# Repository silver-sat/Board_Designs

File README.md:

# Board_Designs
KiCAD files for PC Board Designs
<br><br><strong>Due to technical issues, each board has been moved to their own repositories. Here are the links:</strong>
|Repository Links|                                              |
|--------------|------------------------------------------------|
| Avionics     | https://github.com/silver-sat/Avionics_Board   |
| Payload      | https://github.com/silver-sat/Payload_Board    |
| Radio        | https://github.com/silver-sat/Radio_Board      |

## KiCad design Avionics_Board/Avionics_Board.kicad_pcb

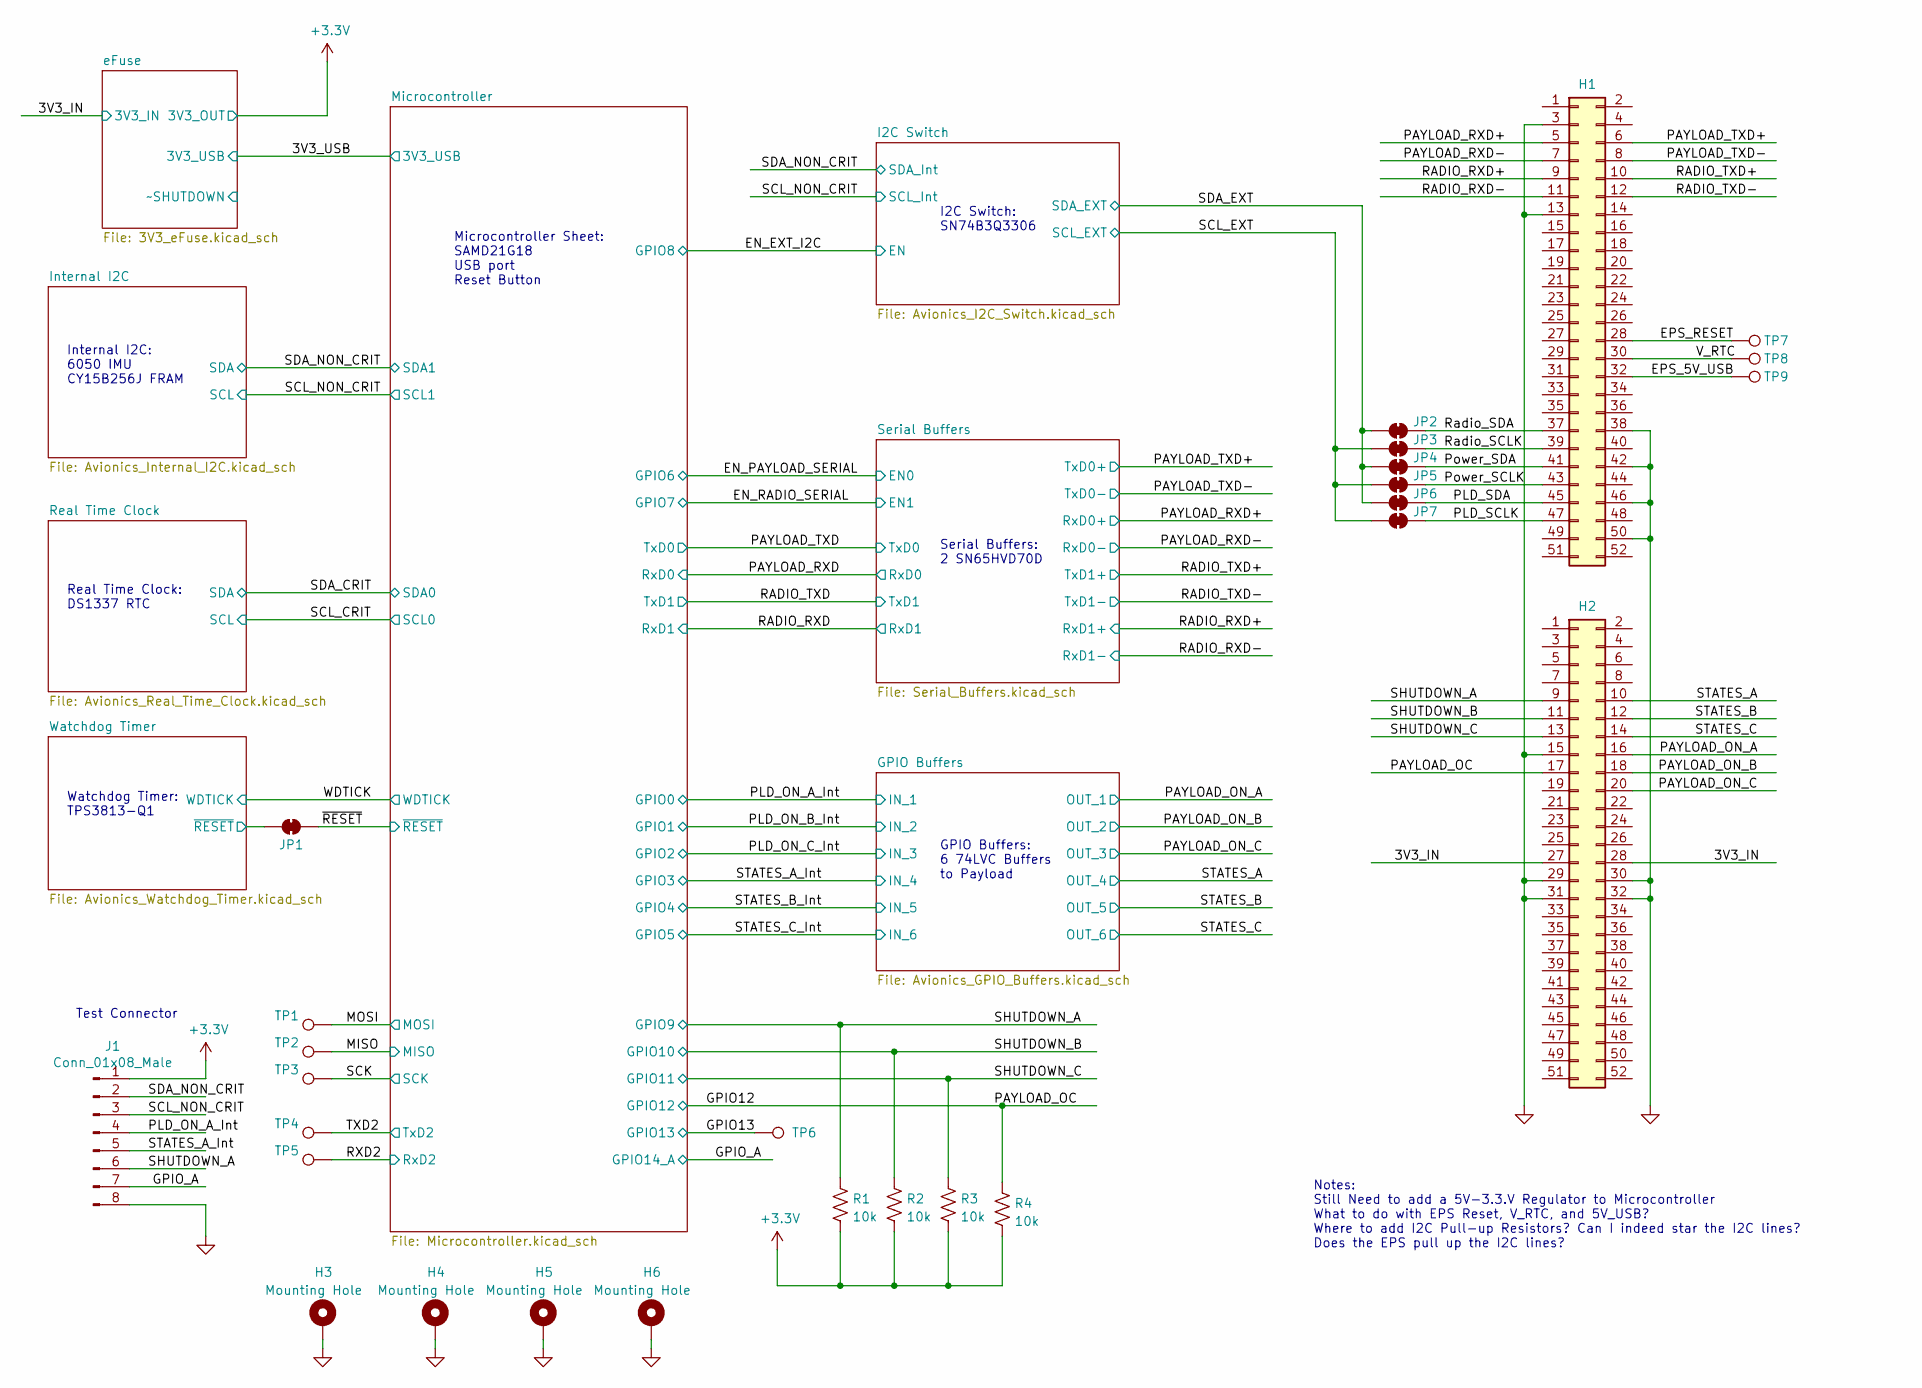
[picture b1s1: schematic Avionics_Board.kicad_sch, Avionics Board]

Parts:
H1, H2: Conn_02x26_Odd_Even; TheBus2x26; Part_Number ESQ-126-37-G-D
H3, H4, H5, H6: Mounting Hole; MountingHole_3.2mm_M3_Pad
J1: Conn_01x08_Male; PinHeader_1x08_P2.54mm_Vertical
JP1, JP2, JP3, JP4, JP5, JP6, JP7: SolderJumper_2_Bridged; SolderJumper-2_P1.3mm_Open_RoundedPad1.0x1.5mm
R1, R2, R3, R4: 10k; R_0603_1608Metric
TP1: MOSI; TestPoint_Pad_2.0x2.0mm
TP2: MISO; TestPoint_Pad_2.0x2.0mm
TP3: SCK; TestPoint_Pad_2.0x2.0mm
TP4: TXD2; TestPoint_Pad_2.0x2.0mm
TP5: RXD2; TestPoint_Pad_2.0x2.0mm
TP6: GPIO13; TestPoint_Pad_2.0x2.0mm
TP7: EPS_RESET; TestPoint_Pad_2.0x2.0mm
TP8: V_RTC; TestPoint_Pad_2.0x2.0mm
TP9: EPS_5V_USB; TestPoint_Pad_2.0x2.0mm

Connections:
+3V3: J1.1, R1.2, R2.2, R3.2, R4.2; also elsewhere on the board
/3V3_IN: H2.27, H2.28; also elsewhere on the board
/EPS_5V_USB: H1.32, TP9.1
/EPS_RESET: H1.28, TP7.1
/GPIO12: H2.17, R4.1; also elsewhere on the board
/GPIO13: TP6.1; also elsewhere on the board
/GPIO_A: J1.7; also elsewhere on the board
/MISO: TP2.1; also elsewhere on the board
/MOSI: TP1.1; also elsewhere on the board
/PAYLOAD_ON_A: H2.16; also elsewhere on the board
/PAYLOAD_ON_B: H2.18; also elsewhere on the board
/PAYLOAD_ON_C: H2.20; also elsewhere on the board
/PAYLOAD_RXD+: H1.5; also elsewhere on the board
/PAYLOAD_RXD-: H1.7; also elsewhere on the board
/PAYLOAD_TXD+: H1.6; also elsewhere on the board
/PAYLOAD_TXD-: H1.8; also elsewhere on the board
/PLD_ON_A_Int: J1.4; also elsewhere on the board
/PLD_SCLK: H1.47, JP7.2 (B)
/PLD_SDA: H1.45, JP6.2 (B)
/Power_SCLK: H1.43, JP5.2 (B)
/Power_SDA: H1.41, JP4.2 (B)
/RADIO_RXD+: H1.9; also elsewhere on the board
/RADIO_RXD-: H1.11; also elsewhere on the board
/RADIO_TXD+: H1.10; also elsewhere on the board
/RADIO_TXD-: H1.12; also elsewhere on the board
/RXD2: TP5.1; also elsewhere on the board
/Radio_SCLK: H1.39, JP3.2 (B)
/Radio_SDA: H1.37, JP2.2 (B)
/SCK: TP3.1; also elsewhere on the board
/SCL_EXT: JP3.1 (A), JP5.1 (A), JP7.1 (A); also elsewhere on the board
/SCL_NON_CRIT: J1.3; also elsewhere on the board
/SDA_EXT: JP2.1 (A), JP4.1 (A), JP6.1 (A); also elsewhere on the board
/SDA_NON_CRIT: J1.2; also elsewhere on the board
/SHUTDOWN_A: H2.9, J1.6, R1.1; also elsewhere on the board
/SHUTDOWN_B: H2.11, R2.1; also elsewhere on the board
/SHUTDOWN_C: H2.13, R3.1; also elsewhere on the board
/STATES_A: H2.10; also elsewhere on the board
/STATES_A_Int: J1.5; also elsewhere on the board
/STATES_B: H2.12; also elsewhere on the board
/STATES_C: H2.14; also elsewhere on the board
/TXD2: TP4.1; also elsewhere on the board
/V_RTC: H1.30, TP8.1
/Watchdog Timer/~RESET: JP1.1 (A); also elsewhere on the board
/~RESET: JP1.2 (B); also elsewhere on the board
GND: H1.3, H1.13, H1.38, H1.42, H1.46, H1.50, H2.15, H2.29, H2.30, H2.31, H2.32, H3.1, H4.1, H5.1, H6.1, J1.8; also elsewhere on the board

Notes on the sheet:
GPIO Buffers: 6 74LVC Buffers to Payload
Serial Buffers: 2 SN65HVD70D
Watchdog Timer: TPS3813-Q1
Real Time Clock: DS1337 RTC
Microcontroller Sheet: SAMD21G18 USB port Reset Button
Notes: Still Need to add a 5V-3.3.V Regulator to Microcontroller What to do with EPS Reset, V_RTC, and 5V_USB? Where to add I2C Pull-up Resistors? Can I indeed star the I2C lines? Does the EPS pull up the I2C lines?
Internal I2C: 6050 IMU CY15B256J FRAM
I2C Switch: SN74B3Q3306
Test Connector

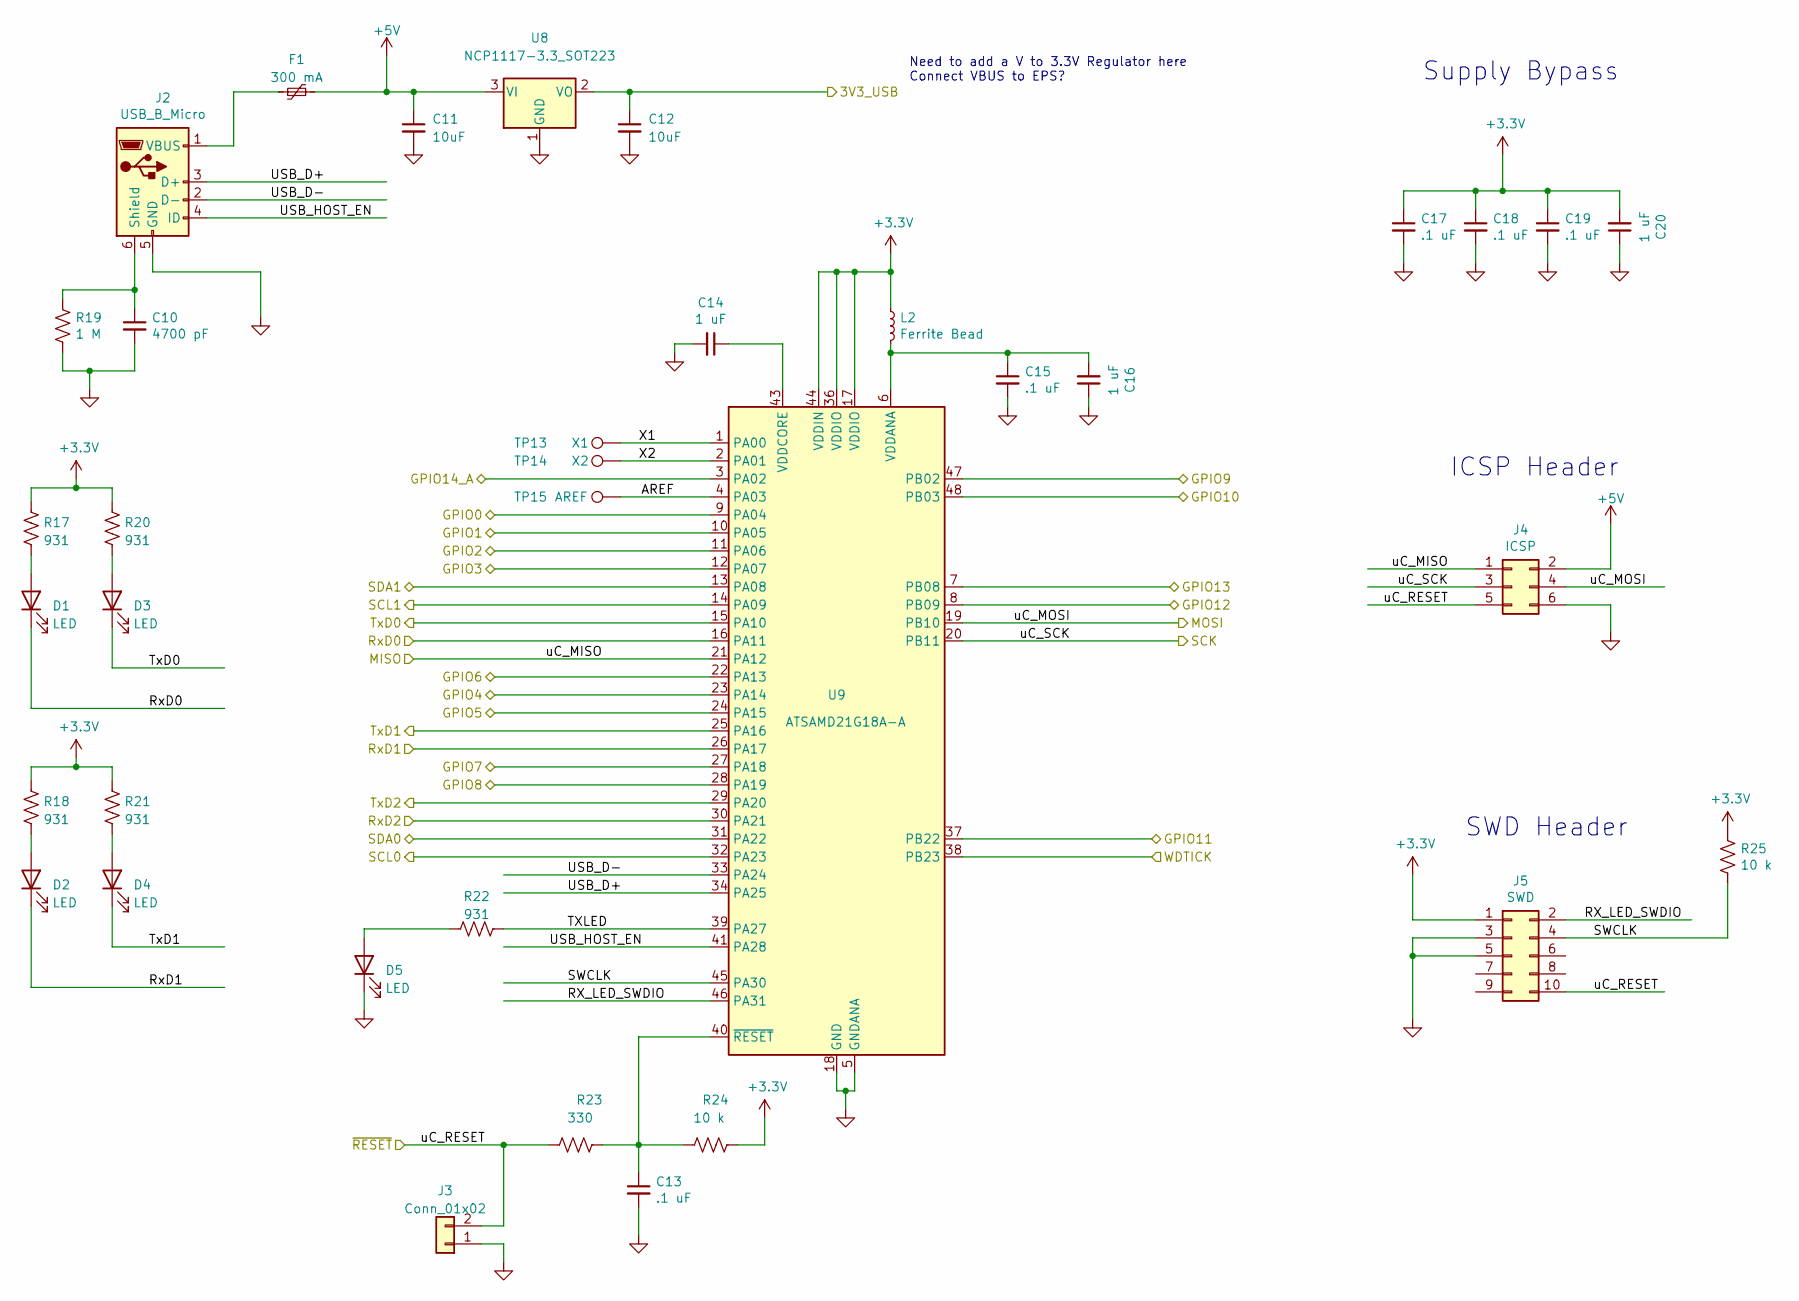
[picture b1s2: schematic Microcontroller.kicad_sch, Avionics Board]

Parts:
C10: 4700 pF; C_0603_1608Metric
C11, C12: 10uF; C_2220_5650Metric_Pad1.97x5.40mm_HandSolder
C13, C15, C17, C18, C19: .1 uF; C_0603_1608Metric
C14, C16, C20: 1 uF; C_1206_3216Metric; Part_Number 12065C105M4Z2A
D1, D2, D3, D4, D5: LED; LED_D3.0mm_Horizontal_O1.27mm_Z2.0mm
F1: 300 mA; Fuse_0805_2012Metric; Part_Number PICOASMDC012S-2
J2: USB_B_Micro; USB_Micro-B_Molex-105017-0001; Part_Number 105017-0001
J3: Conn_01x02; PinHeader_1x02_P2.54mm_Vertical
J4: ICSP; PinHeader_2x03_P2.54mm_Vertical
J5: SWD; PinHeader_2x05_P1.27mm_Vertical_SMD; Part_Number 4048
L2: Ferrite Bead; L_0603_1608Metric; Part_Number BLM18SP102SH1D
R17, R18, R20, R21, R22: 931; R_0603_1608Metric; Part_Number ERJ-3EKF9310V
R19: 1 M; R_0603_1608Metric
R23: 330; R_0603_1608Metric
R24, R25: 10 k; R_0603_1608Metric
TP13: X1; TestPoint_Pad_2.0x2.0mm
TP14: X2; TestPoint_Pad_2.0x2.0mm
TP15: AREF; TestPoint_Pad_2.0x2.0mm
U8: NCP1117-3.3_SOT223; SOT-223-3_TabPin2
U9: ATSAMD21G18A-A; TQFP-48_7x7mm_P0.5mm

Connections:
+3V3: C17.1, C18.1, C19.1, C20.2, J5.1, L2.1, R17.1, R18.1, R20.1, R21.1, R24.1, R25.1, U9.17 (VDDIO), U9.36 (VDDIO), U9.44 (VDDIN); also elsewhere on the board
+5V: C11.1, F1.2, J4.2, U8.3 (VI)
/3V3_USB: C12.1, U8.2 (VO); also elsewhere on the board
/EN_EXT_I2C: U9.28 (PA19); also elsewhere on the board
/EN_PAYLOAD_SERIAL: U9.22 (PA13); also elsewhere on the board
/EN_RADIO_SERIAL: U9.27 (PA18); also elsewhere on the board
/GPIO12: U9.8 (PB09); also elsewhere on the board
/GPIO13: U9.7 (PB08); also elsewhere on the board
/GPIO_A: U9.3 (PA02); also elsewhere on the board
/MISO: J4.1, U9.21 (PA12); also elsewhere on the board
/MOSI: J4.4, U9.19 (PB10); also elsewhere on the board
/Microcontroller/AREF: TP15.1, U9.4 (PA03)
/Microcontroller/RX_LED_SWDIO: J5.2, U9.46 (PA31)
/Microcontroller/SWCLK: J5.4, R25.2, U9.45 (PA30)
/Microcontroller/TXLED: R22.2, U9.39 (PA27)
/Microcontroller/USB_D+: J2.3 (D+), U9.34 (PA25)
/Microcontroller/USB_D-: J2.2 (D-), U9.33 (PA24)
/Microcontroller/USB_HOST_EN: J2.4 (ID), U9.41 (PA28)
/Microcontroller/X1: TP13.1, U9.1 (PA00)
/Microcontroller/X2: TP14.1, U9.2 (PA01)
/PAYLOAD_RXD: D1.1 (K), U9.16 (PA11); also elsewhere on the board
/PAYLOAD_TXD: D3.1 (K), U9.15 (PA10); also elsewhere on the board
/PLD_ON_A_Int: U9.9 (PA04); also elsewhere on the board
/PLD_ON_B_Int: U9.10 (PA05); also elsewhere on the board
/PLD_ON_C_Int: U9.11 (PA06); also elsewhere on the board
/RADIO_RXD: D2.1 (K), U9.26 (PA17); also elsewhere on the board
/RADIO_TXD: D4.1 (K), U9.25 (PA16); also elsewhere on the board
/RXD2: U9.30 (PA21); also elsewhere on the board
/SCK: J4.3, U9.20 (PB11); also elsewhere on the board
/SCL_CRIT: U9.32 (PA23); also elsewhere on the board
/SCL_NON_CRIT: U9.14 (PA09); also elsewhere on the board
/SDA_CRIT: U9.31 (PA22); also elsewhere on the board
/SDA_NON_CRIT: U9.13 (PA08); also elsewhere on the board
/SHUTDOWN_A: U9.47 (PB02); also elsewhere on the board
/SHUTDOWN_B: U9.48 (PB03); also elsewhere on the board
/SHUTDOWN_C: U9.37 (PB22); also elsewhere on the board
/STATES_A_Int: U9.12 (PA07); also elsewhere on the board
/STATES_B_Int: U9.23 (PA14); also elsewhere on the board
/STATES_C_Int: U9.24 (PA15); also elsewhere on the board
/TXD2: U9.29 (PA20); also elsewhere on the board
/WDTICK: U9.38 (PB23); also elsewhere on the board
/~RESET: J3.2, J4.5, J5.10, R23.2; also elsewhere on the board
GND: C10.2, C11.2, C12.2, C13.2, C14.2, C15.2, C16.1, C17.2, C18.2, C19.2, C20.1, D5.1 (K), J2.5 (GND), J3.1, J4.6, J5.3, J5.5, R19.2, U8.1 (GND), U9.5 (GNDANA), U9.18 (GND), U9.35 (GND), U9.42 (GND); also elsewhere on the board
unnamed: C10.1, J2.6 (Shield), R19.1
unnamed: C13.1, R23.1, R24.2, U9.40 (~RESET)
unnamed: C14.1, U9.43 (VDDCORE)
unnamed: C15.1, C16.2, L2.2, U9.6 (VDDANA)
unnamed: D1.2 (A), R17.2
unnamed: D2.2 (A), R18.2
unnamed: D3.2 (A), R20.2
unnamed: D4.2 (A), R21.2
unnamed: D5.2 (A), R22.1
unnamed: F1.1, J2.1 (VBUS)

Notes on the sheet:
Need to add a V to 3.3V Regulator here Connect VBUS to EPS?
ICSP Header
SWD Header
Supply Bypass

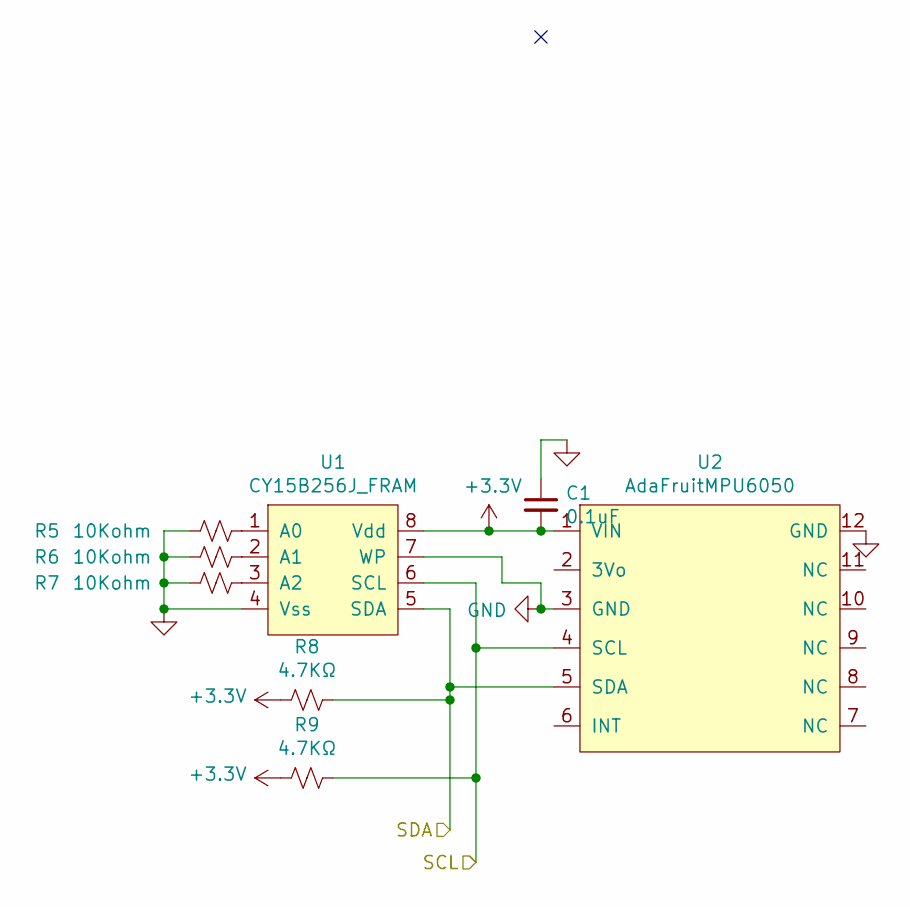
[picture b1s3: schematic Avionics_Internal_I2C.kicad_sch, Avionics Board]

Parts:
C1: 0.1uF; C_0603_1608Metric
R5, R6, R7: 10Kohm; R_0603_1608Metric
R8, R9: 4.7KΩ; R_0603_1608Metric
U1: CY15B256J_FRAM; SOP-8_5.28x5.23mm_P1.27mm
U2: AdaFruitMPU6050; MPU_6050

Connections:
+3V3: C1.2, R8.2, R9.2, U1.8 (Vdd), U2.1 (VIN); also elsewhere on the board
/SCL_NON_CRIT: R9.1, U1.6 (SCL), U2.4 (SCL); also elsewhere on the board
/SDA_NON_CRIT: R8.1, U1.5 (SDA), U2.5 (SDA); also elsewhere on the board
GND: C1.1, R5.2, R6.2, R7.2, U1.4 (Vss), U1.7 (WP), U2.3 (GND), U2.12 (GND); also elsewhere on the board
unnamed: R5.1, U1.1 (A0)
unnamed: R6.1, U1.2 (A1)
unnamed: R7.1, U1.3 (A2)

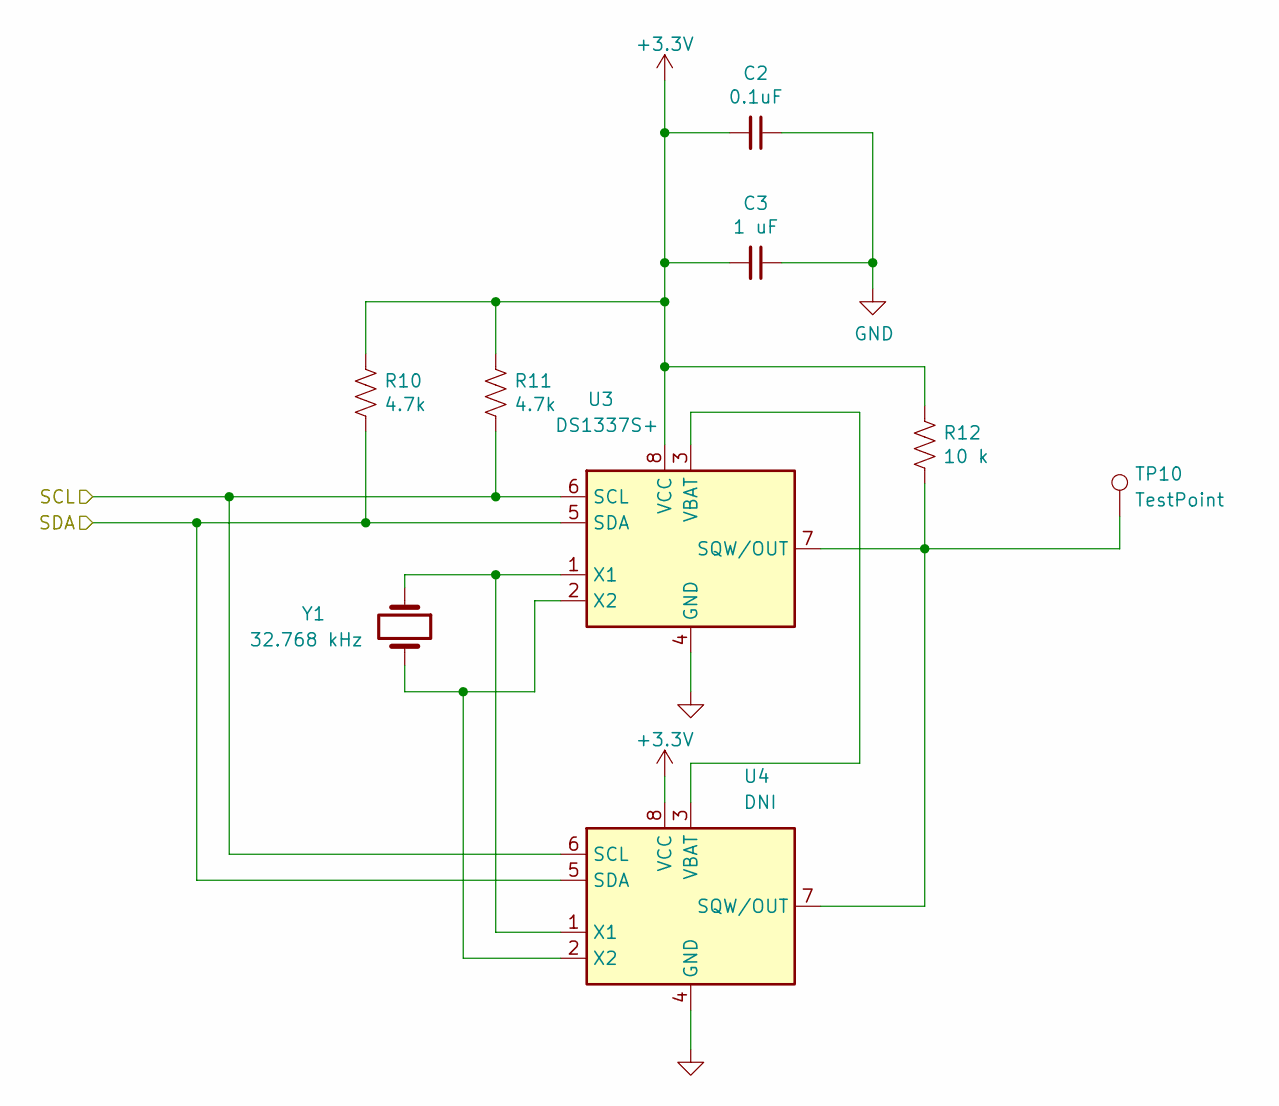
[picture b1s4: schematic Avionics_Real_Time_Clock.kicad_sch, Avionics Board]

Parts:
C2: 0.1uF; C_0603_1608Metric
C3: 1 uF; C_1206_3216Metric; Part_Number 12065C105M4Z2A
R10, R11: 4.7k; R_0603_1608Metric
R12: 10 k; R_0603_1608Metric
TP10: TestPoint; TestPoint_Pad_2.0x2.0mm
U3: DS1337S+; SOIC-8_3.9x4.9mm_P1.27mm; Part_Number DS1337S+T&R
U4: DNI; DIP-8_W7.62mm; Part_Number DS1337+
Y1: 32.768 kHz; Crystal_SMD_3215-2Pin_3.2x1.5mm; Part_Number ECS-.327-6-34QCS-TR

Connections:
+3V3: C2.2, C3.2, R10.1, R11.1, R12.1, U3.8 (VCC), U4.8 (VCC); also elsewhere on the board
/SCL_CRIT: R11.2, U3.6 (SCL), U4.6 (SCL); also elsewhere on the board
/SDA_CRIT: R10.2, U3.5 (SDA), U4.5 (SDA); also elsewhere on the board
GND: C2.1, C3.1, U3.4 (GND), U4.4 (GND); also elsewhere on the board
unnamed: R12.2, TP10.1, U3.7 (SQW/OUT), U4.7 (SQW/OUT)
unnamed: U3.1 (X1), U4.1 (X1), Y1.1
unnamed: U3.2 (X2), U4.2 (X2), Y1.2
unnamed: U3.3 (VBAT), U4.3 (VBAT)

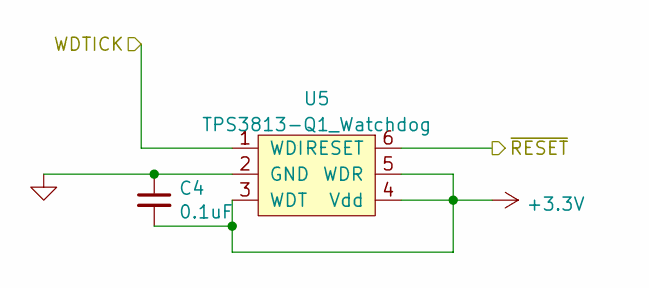
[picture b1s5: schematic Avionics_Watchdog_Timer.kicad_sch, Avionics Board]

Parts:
C4: 0.1uF; C_0603_1608Metric
U5: TPS3813-Q1_Watchdog; SOT-23-6

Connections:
+3V3: C4.2, U5.3 (WDT), U5.4 (Vdd), U5.5 (WDR); also elsewhere on the board
/WDTICK: U5.1 (WDI); also elsewhere on the board
/Watchdog Timer/~RESET: U5.6 (RESET); also elsewhere on the board
GND: C4.1, U5.2 (GND); also elsewhere on the board

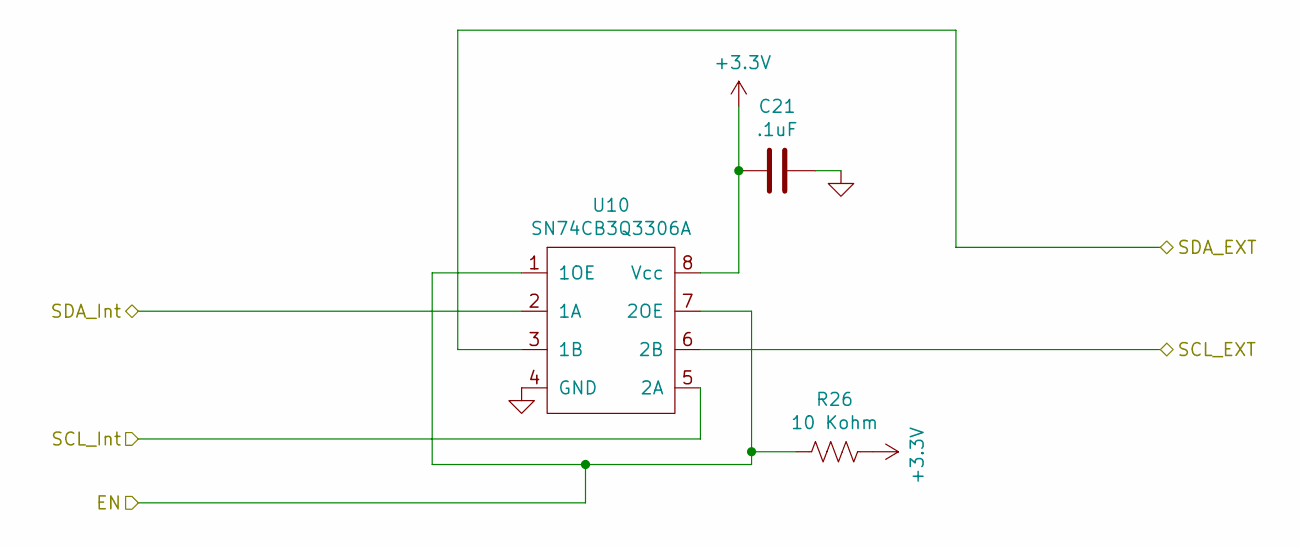
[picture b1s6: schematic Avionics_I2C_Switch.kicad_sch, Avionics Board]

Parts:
C21: .1uF; C_0603_1608Metric
R26: 10 Kohm; R_0603_1608Metric
U10: SN74CB3Q3306A; TSSOP-8_4.4x3mm_P0.65mm

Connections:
+3V3: C21.1, R26.1, U10.8 (Vcc); also elsewhere on the board
/EN_EXT_I2C: R26.2, U10.1 (1OE), U10.7 (2OE); also elsewhere on the board
/SCL_EXT: U10.6 (2B); also elsewhere on the board
/SCL_NON_CRIT: U10.5 (2A); also elsewhere on the board
/SDA_EXT: U10.3 (1B); also elsewhere on the board
/SDA_NON_CRIT: U10.2 (1A); also elsewhere on the board
GND: C21.2, U10.4 (GND); also elsewhere on the board

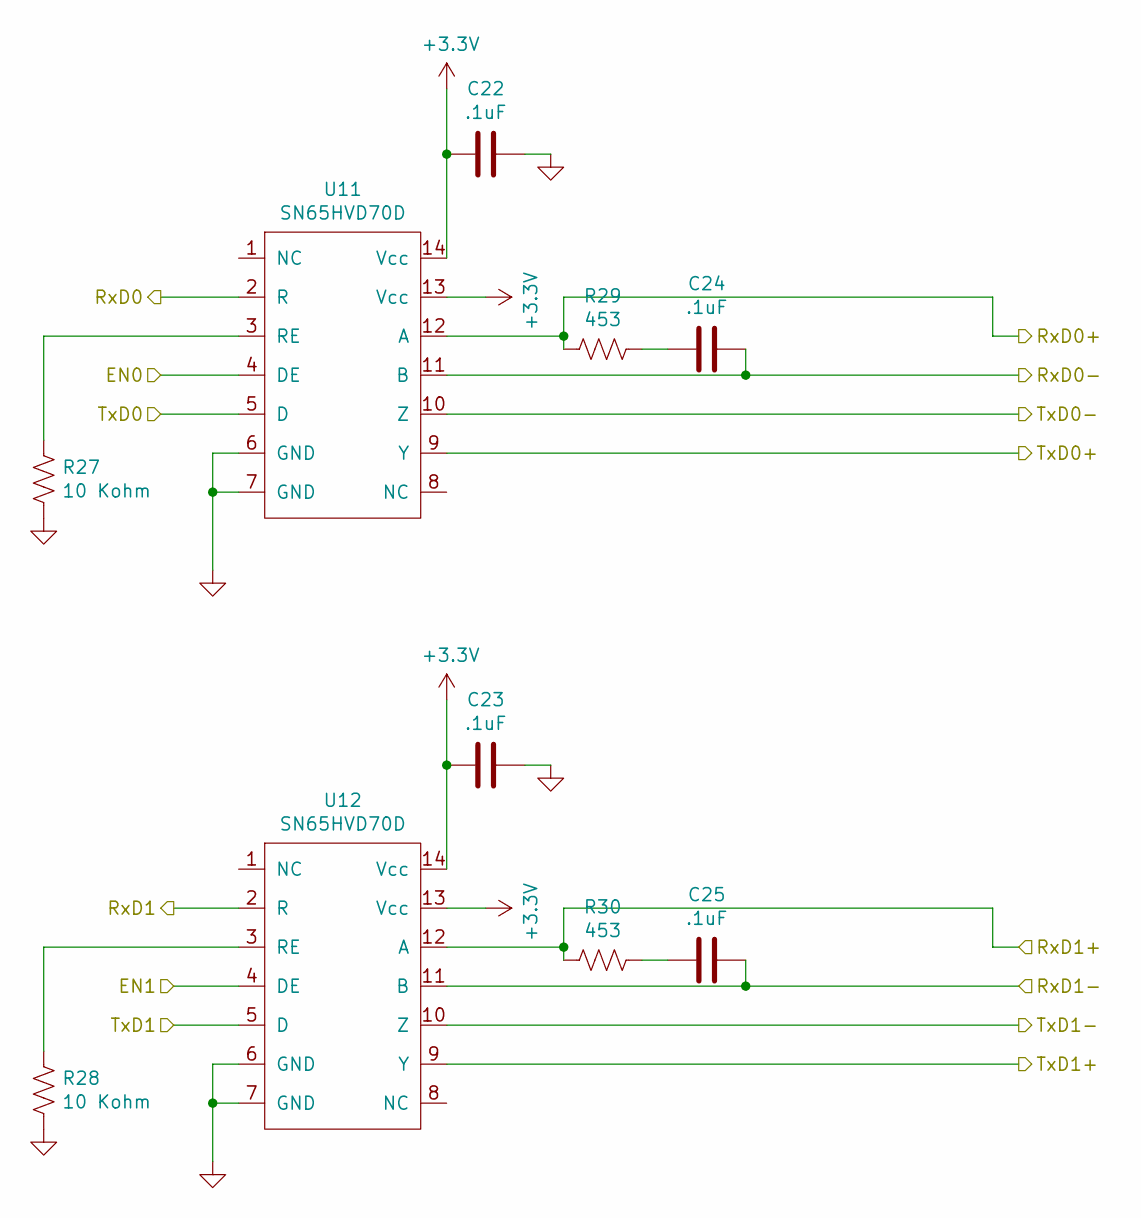
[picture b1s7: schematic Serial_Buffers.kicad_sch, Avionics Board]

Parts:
C22, C23, C24, C25: .1uF; C_0603_1608Metric
R27, R28: 10 Kohm; R_0603_1608Metric
R29, R30: 453; R_0603_1608Metric
U11, U12: SN65HVD70D; SOIC-14_3.9x8.7mm_P1.27mm

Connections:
+3V3: C22.1, C23.1, U11.13 (Vcc), U11.14 (Vcc), U12.13 (Vcc), U12.14 (Vcc); also elsewhere on the board
/EN_PAYLOAD_SERIAL: U11.4 (DE); also elsewhere on the board
/EN_RADIO_SERIAL: U12.4 (DE); also elsewhere on the board
/PAYLOAD_RXD: U11.2 (R); also elsewhere on the board
/PAYLOAD_RXD+: R29.2, U11.12 (A); also elsewhere on the board
/PAYLOAD_RXD-: C24.2, U11.11 (B); also elsewhere on the board
/PAYLOAD_TXD: U11.5 (D); also elsewhere on the board
/PAYLOAD_TXD+: U11.9 (Y); also elsewhere on the board
/PAYLOAD_TXD-: U11.10 (Z); also elsewhere on the board
/RADIO_RXD: U12.2 (R); also elsewhere on the board
/RADIO_RXD+: R30.2, U12.12 (A); also elsewhere on the board
/RADIO_RXD-: C25.2, U12.11 (B); also elsewhere on the board
/RADIO_TXD: U12.5 (D); also elsewhere on the board
/RADIO_TXD+: U12.9 (Y); also elsewhere on the board
/RADIO_TXD-: U12.10 (Z); also elsewhere on the board
GND: C22.2, C23.2, R27.2, R28.2, U11.6 (GND), U11.7 (GND), U12.6 (GND), U12.7 (GND); also elsewhere on the board
unnamed: C24.1, R29.1
unnamed: C25.1, R30.1
unnamed: R27.1, U11.3 (RE)
unnamed: R28.1, U12.3 (RE)

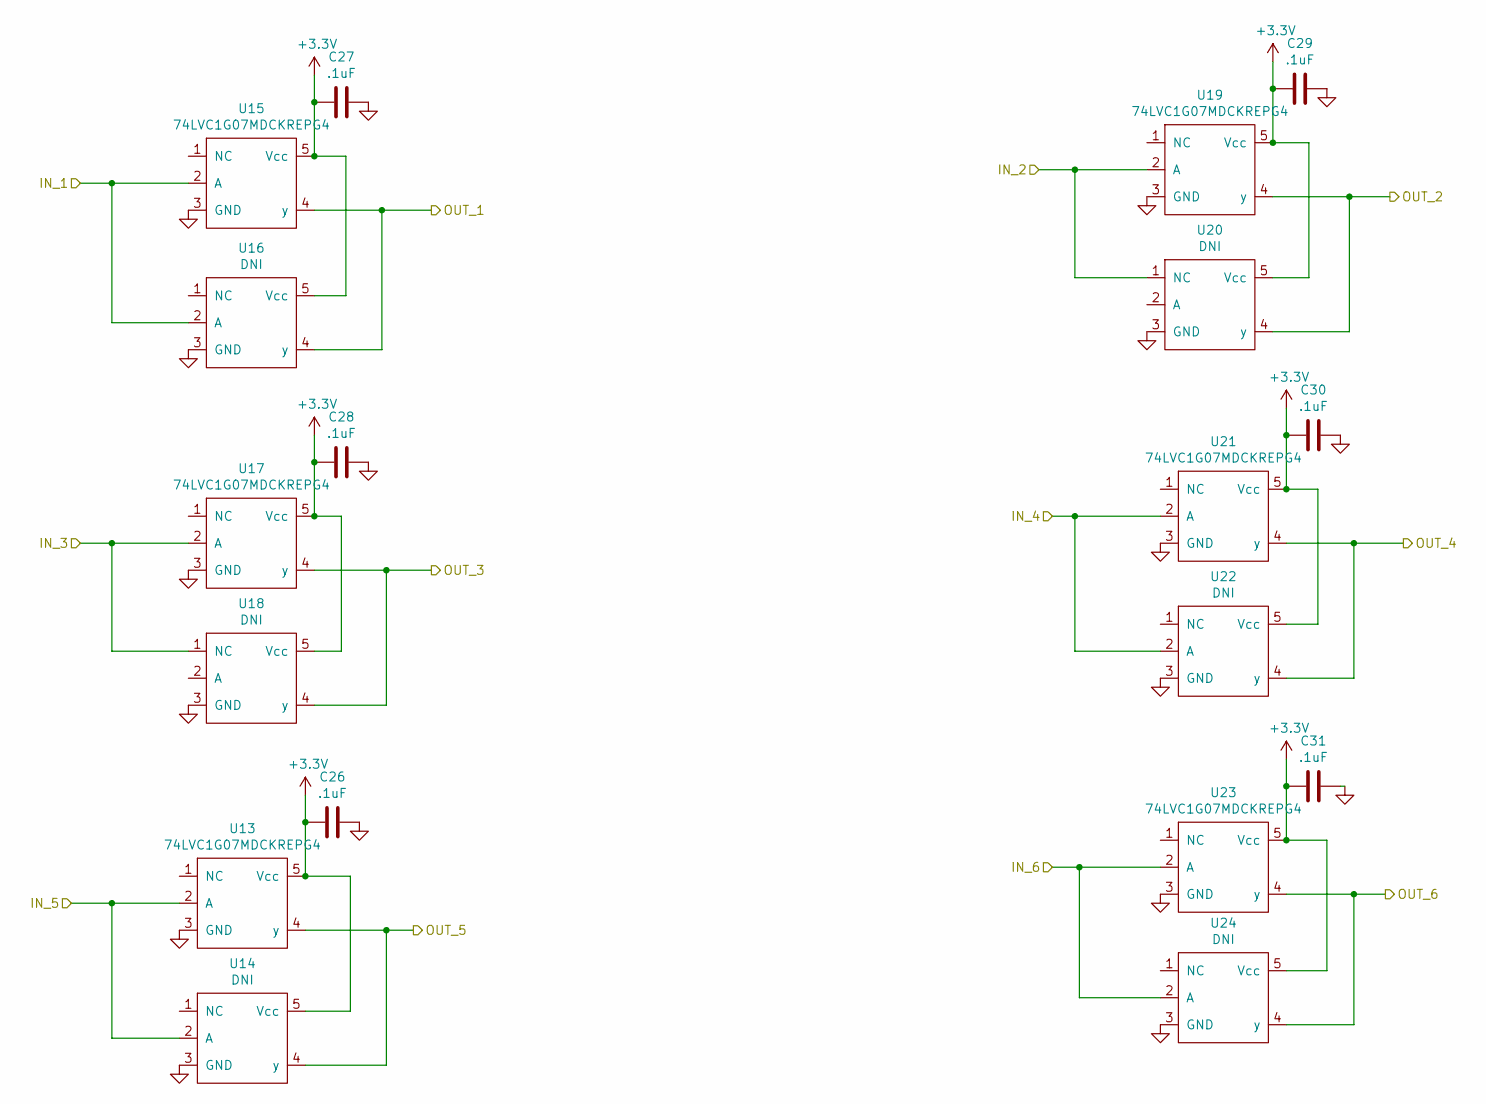
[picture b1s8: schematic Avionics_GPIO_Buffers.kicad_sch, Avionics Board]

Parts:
C26, C27, C28, C29, C30, C31: .1uF; C_0603_1608Metric
U13, U15, U17, U19, U21, U23: 74LVC1G07MDCKREPG4; SOT-353_SC-70-5
U14, U16, U18, U20, U22, U24: DNI; SOT-23-5

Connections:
+3V3: C26.2, C27.2, C28.2, C29.2, C30.2, C31.2, U13.5 (Vcc), U14.5 (Vcc), U15.5 (Vcc), U16.5 (Vcc), U17.5 (Vcc), U18.5 (Vcc), U19.5 (Vcc), U20.5 (Vcc), U21.5 (Vcc), U22.5 (Vcc), U23.5 (Vcc), U24.5 (Vcc); also elsewhere on the board
/PAYLOAD_ON_A: U15.4 (y), U16.4 (y); also elsewhere on the board
/PAYLOAD_ON_B: U19.4 (y), U20.4 (y); also elsewhere on the board
/PAYLOAD_ON_C: U17.4 (y), U18.4 (y); also elsewhere on the board
/PLD_ON_A_Int: U15.2 (A), U16.2 (A); also elsewhere on the board
/PLD_ON_B_Int: U19.2 (A), U20.1 (NC); also elsewhere on the board
/PLD_ON_C_Int: U17.2 (A), U18.1 (NC); also elsewhere on the board
/STATES_A: U21.4 (y), U22.4 (y); also elsewhere on the board
/STATES_A_Int: U21.2 (A), U22.2 (A); also elsewhere on the board
/STATES_B: U13.4 (y), U14.4 (y); also elsewhere on the board
/STATES_B_Int: U13.2 (A), U14.2 (A); also elsewhere on the board
/STATES_C: U23.4 (y), U24.4 (y); also elsewhere on the board
/STATES_C_Int: U23.2 (A), U24.2 (A); also elsewhere on the board
GND: C26.1, C27.1, C28.1, C29.1, C30.1, C31.1, U13.3 (GND), U14.3 (GND), U15.3 (GND), U16.3 (GND), U17.3 (GND), U18.3 (GND), U19.3 (GND), U20.3 (GND), U21.3 (GND), U22.3 (GND), U23.3 (GND), U24.3 (GND); also elsewhere on the board

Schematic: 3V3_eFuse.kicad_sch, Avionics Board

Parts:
C5, C7, C8, C9: 0.1 uF; C_0603_1608Metric
C6: 10 uF; C_2220_5650Metric_Pad1.97x5.40mm_HandSolder; Part_Number 22205C106K4Z4A
L1: Ferrite Bead; L_0603_1608Metric; Part_Number BLM18SP102SH1D
R13, R14, R15, R16: 10 k; R_0603_1608Metric; Part_Number ERJ-3EKF1002V
TP11, TP12: TestPoint; TestPoint_Pad_2.0x2.0mm
U6: FPF2000; SOT-353_SC-70-5
U7: TPS2105MDBVREP; SOT-23-5

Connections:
+3V3: C9.1, TP12.1, U7.4 (OUT); also elsewhere on the board
/3V3_IN: C5.1, L1.1; also elsewhere on the board
/3V3_USB: U7.3 (IN2); also elsewhere on the board
/eFuse/3V3_IN_FILT: C6.1, L1.2, R13.1, R14.1, R15.1, U6.5 (VIN)
/eFuse/~SHUTDOWN: R13.2, U6.4 (ON)
GND: C5.2, C6.2, C7.2, C8.2, C9.2, R16.2, U6.2 (GND), U7.2 (GND); also elsewhere on the board
unnamed: C7.1, C8.1, R16.1, TP11.1, U6.1 (VOUT), U7.5 (IN1)
unnamed: R14.2, U7.1 (EN)
unnamed: R15.2, U6.3 (FLAGB)

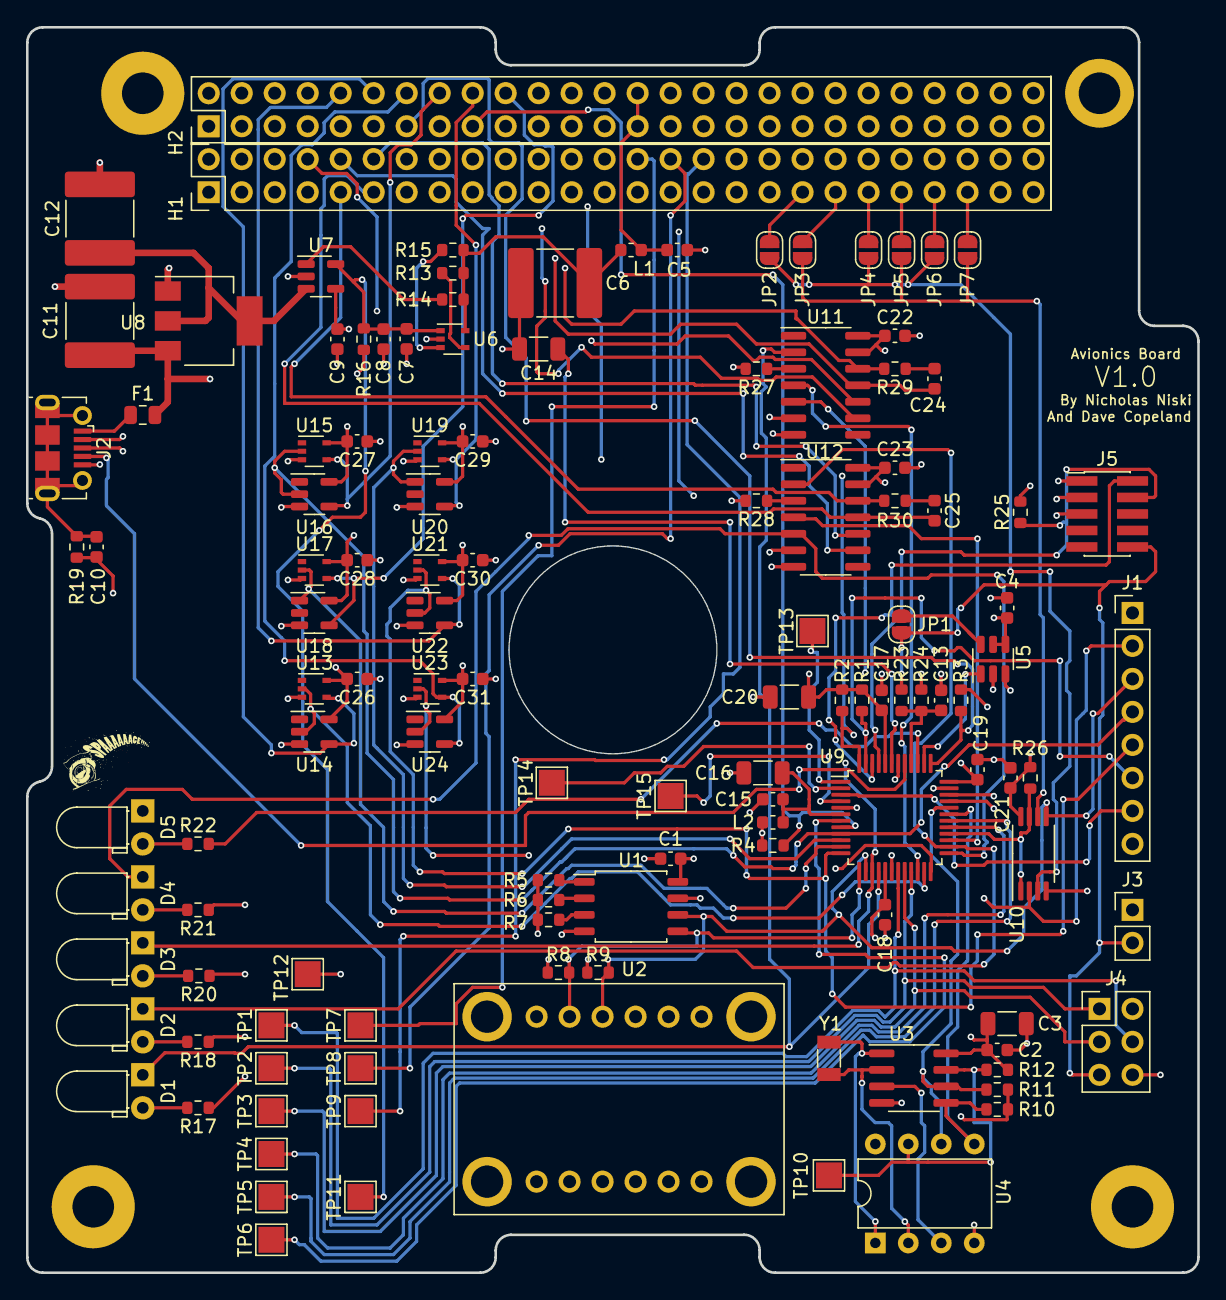
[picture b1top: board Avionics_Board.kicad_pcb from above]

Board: 4 copper layers, 90.2 x 95.9 mm, 127 parts (0 on the bottom side), 96 nets.
